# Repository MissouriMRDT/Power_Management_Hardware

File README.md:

# Power_Management_Hardware
Monitors health of the battery and distributes power to the rover's electronics

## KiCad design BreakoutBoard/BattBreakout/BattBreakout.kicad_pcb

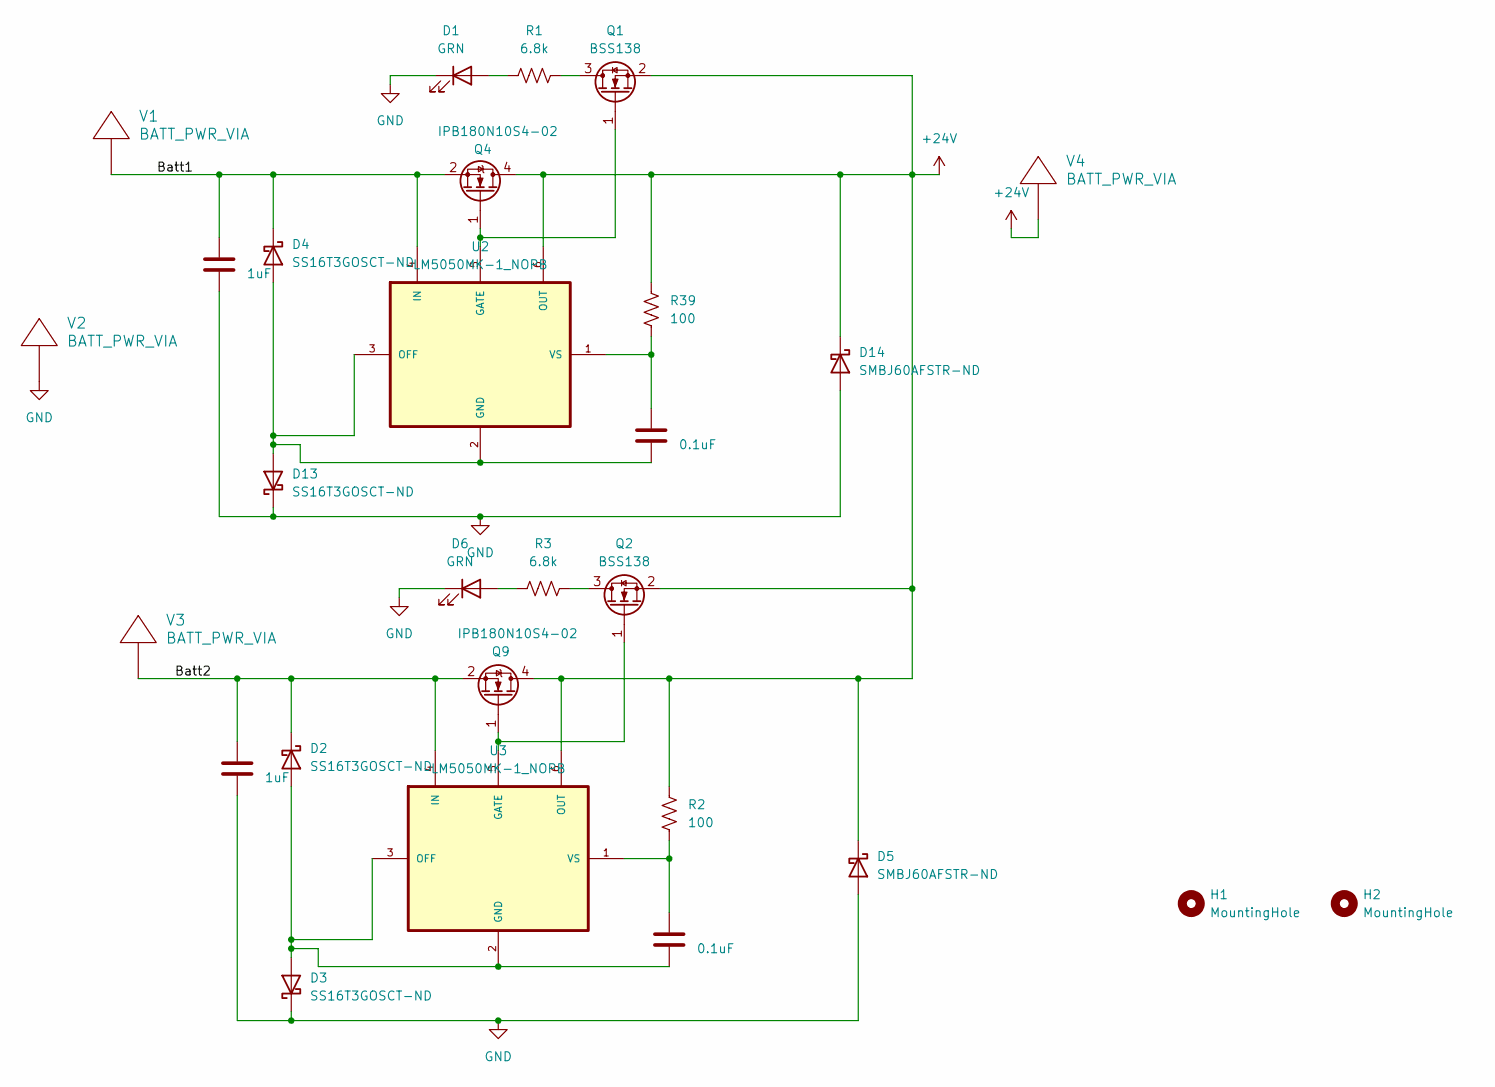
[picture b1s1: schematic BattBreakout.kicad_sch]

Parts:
C5, C11: 1uF; C_0603_1608Metric_Pad1.08x0.95mm_HandSolder
C10, C12: 0.1uF; C_0603_1608Metric_Pad1.08x0.95mm_HandSolder
D1, D6: GRN; LED_0201_0603Metric_Pad0.64x0.40mm_HandSolder
D2, D3, D4, D13: SS16T3GOSCT-ND; D_SMA
D5, D14: SMBJ60AFSTR-ND; D_SMB
H1, H2: MountingHole; 4_40_Hole_Corner
Q1, Q2: BSS138; SOT-23W_Handsoldering
Q4, Q9: IPB180N10S4-02; TO-263-6
R1, R3: 6.8k; R_0201_0603Metric_Pad0.64x0.40mm_HandSolder
R2, R39: 100; R_0201_0603Metric_Pad0.64x0.40mm_HandSolder
U2, U3: LM5050MK-1_NOPB; SOT95P280X110-6N
V1, V2, V3, V4: BATT_PWR_VIA

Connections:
+24V: D5.1 (K), D14.1 (K), Q1.2 (S), Q2.2 (S), Q4.4 (D), Q9.4 (D), R2.2, R39.2, U2.6 (OUT), U3.6 (OUT), V4.1
/Batt1: C11.1, D4.1 (K), Q4.2 (S), Q4.3 (S), Q4.5 (S), Q4.6 (S), Q4.7 (S), U2.4 (IN), V1.1
/Batt2: C5.1, D2.1 (K), Q9.2 (S), Q9.3 (S), Q9.5 (S), Q9.6 (S), Q9.7 (S), U3.4 (IN), V3.1
GND: C5.2, C11.2, D1.1 (K), D3.1 (K), D5.2 (A), D6.1 (K), D13.1 (K), D14.2 (A), V2.1
unnamed: D1.2 (A), R1.1
unnamed: C10.2, D2.2 (A), D3.2 (A), U3.2 (GND), U3.3 (OFF)
unnamed: D6.2 (A), R3.1
unnamed: C12.2, D4.2 (A), D13.2 (A), U2.2 (GND), U2.3 (OFF)
unnamed: Q1.3 (D), R1.2
unnamed: Q1.1 (G), Q4.1 (G), U2.5 (GATE)
unnamed: Q2.3 (D), R3.2
unnamed: Q2.1 (G), Q9.1 (G), U3.5 (GATE)
unnamed: C12.1, R39.1, U2.1 (VS)
unnamed: C10.1, R2.1, U3.1 (VS)

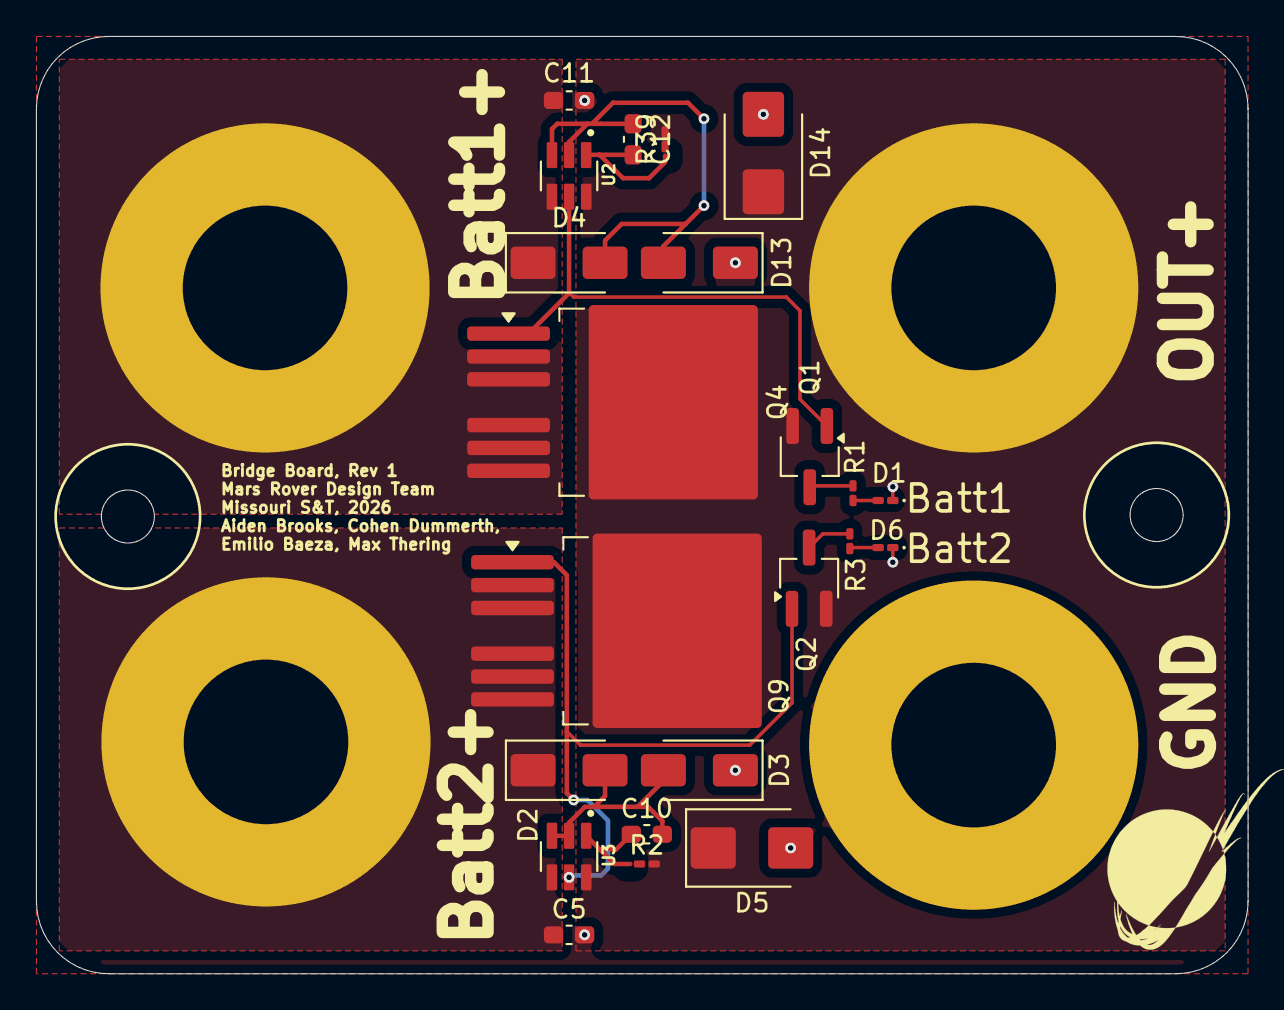
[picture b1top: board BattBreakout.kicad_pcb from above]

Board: 2 copper layers, 67.3 x 52.1 mm, 29 parts (0 on the bottom side), 14 nets.

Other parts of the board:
G1: LOGO; 0_MRDT_Logo_10mm

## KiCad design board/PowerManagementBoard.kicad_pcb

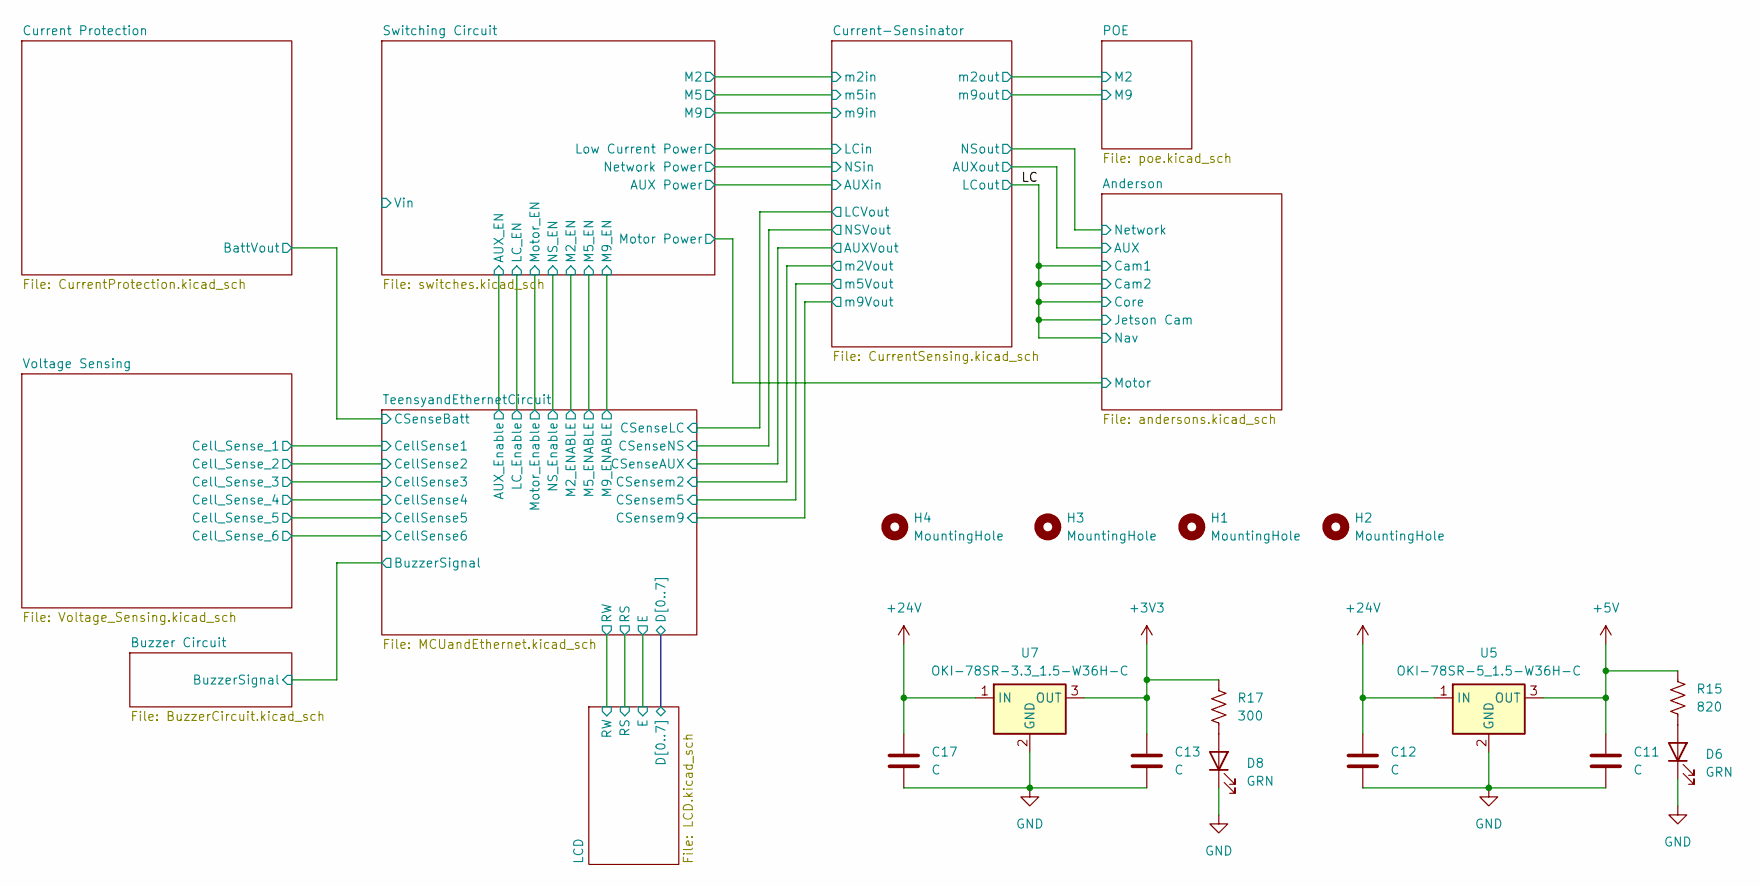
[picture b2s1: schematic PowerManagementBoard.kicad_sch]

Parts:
C11, C12, C13, C17: C; C_0603_1608Metric_Pad1.08x0.95mm_HandSolder
D6, D8: GRN; LED_0603_1608Metric_Pad1.05x0.95mm_HandSolder
H1, H2, H3, H4: MountingHole; 4_40_Hole
R15: 820; R_0603_1608Metric_Pad0.98x0.95mm_HandSolder
R17: 300; R_0603_1608Metric_Pad0.98x0.95mm_HandSolder
U5: OKI-78SR-5_1.5-W36H-C; Converter_DCDC_Murata_OKI-78SR_Horizontal
U7: OKI-78SR-3.3_1.5-W36H-C; Converter_DCDC_Murata_OKI-78SR_Horizontal

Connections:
+3V3: C13.1, R17.1, U7.3 (OUT); also elsewhere on the board
+5V: C11.1, R15.1, U5.3 (OUT); also elsewhere on the board
+24V: C12.1, C17.1, U5.1 (IN), U7.1 (IN); also elsewhere on the board
GND: C11.2, C12.2, C13.2, C17.2, D6.1 (K), D8.1 (K), U5.2 (GND), U7.2 (GND); also elsewhere on the board
unnamed: D6.2 (A), R15.2
unnamed: D8.2 (A), R17.2

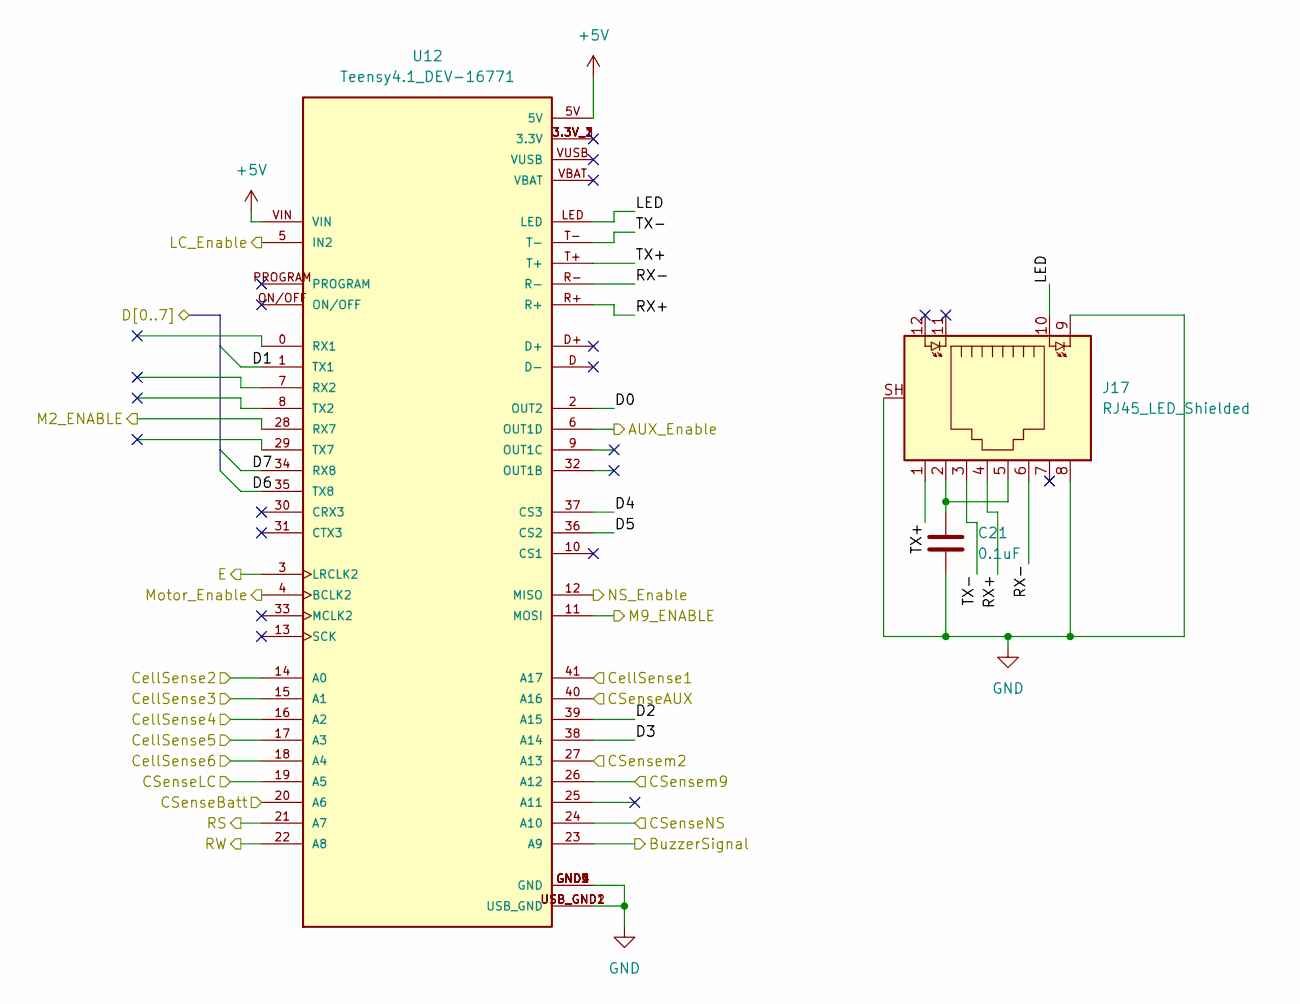
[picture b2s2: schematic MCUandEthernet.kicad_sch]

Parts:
C21: 0.1uF; C_0603_1608Metric_Pad1.08x0.95mm_HandSolder
J17: RJ45_LED_Shielded; RJ45_Teensy
U12: Teensy4.1_DEV-16771; Teensy_4_1_Ethernet; PARTREV 4.1

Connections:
+5V: U12.5V, U12.VIN; also elsewhere on the board
/Buzzer Circuit/BuzzerSignal: U12.23 (A9); also elsewhere on the board
/Current Protection/BattVout: U12.20 (A6); also elsewhere on the board
/Current-Sensinator/AUXVout: U12.40 (A16); also elsewhere on the board
/Current-Sensinator/LCVout: U12.19 (A5); also elsewhere on the board
/Current-Sensinator/NSVout: U12.24 (A10); also elsewhere on the board
/Current-Sensinator/m2Vout: U12.27 (A13); also elsewhere on the board
/Current-Sensinator/m9Vout: U12.26 (A12); also elsewhere on the board
/LCD/D0: U12.2 (OUT2); also elsewhere on the board
/LCD/D1: U12.1 (TX1); also elsewhere on the board
/LCD/D2: U12.39 (A15); also elsewhere on the board
/LCD/D3: U12.38 (A14); also elsewhere on the board
/LCD/D4: U12.37 (CS3); also elsewhere on the board
/LCD/D5: U12.36 (CS2); also elsewhere on the board
/LCD/D6: U12.35 (TX8); also elsewhere on the board
/LCD/D7: U12.34 (RX8); also elsewhere on the board
/LCD/E: U12.3 (LRCLK2); also elsewhere on the board
/LCD/RS: U12.21 (A7); also elsewhere on the board
/LCD/RW: U12.22 (A8); also elsewhere on the board
/Switching Circuit/AUX_EN: U12.6 (OUT1D); also elsewhere on the board
/Switching Circuit/LC_EN: U12.5 (IN2); also elsewhere on the board
/Switching Circuit/M2_EN: U12.28 (RX7); also elsewhere on the board
/Switching Circuit/M9_EN: U12.11 (MOSI); also elsewhere on the board
/Switching Circuit/Motor_EN: U12.4 (BCLK2); also elsewhere on the board
/Switching Circuit/NS_EN: U12.12 (MISO); also elsewhere on the board
/TeensyandEthernetCircuit/CellSense1: U12.41 (A17); also elsewhere on the board
/TeensyandEthernetCircuit/CellSense2: U12.14 (A0); also elsewhere on the board
/TeensyandEthernetCircuit/CellSense3: U12.15 (A1); also elsewhere on the board
/TeensyandEthernetCircuit/CellSense4: U12.16 (A2); also elsewhere on the board
/TeensyandEthernetCircuit/CellSense5: U12.17 (A3); also elsewhere on the board
/TeensyandEthernetCircuit/CellSense6: U12.18 (A4); also elsewhere on the board
/TeensyandEthernetCircuit/LED: J17.10, U12.LED
/TeensyandEthernetCircuit/RX+: J17.4, U12.R+
/TeensyandEthernetCircuit/RX-: J17.6, U12.R-
/TeensyandEthernetCircuit/TX+: J17.1, U12.T+
/TeensyandEthernetCircuit/TX-: J17.3, U12.T-
GND: C21.2, J17.8, J17.9, J17.SH, U12.GND1 (GND), U12.GND2 (GND), U12.GND3 (GND), U12.GND4 (GND), U12.GND5 (GND), U12.USB_GND1 (USB_GND), U12.USB_GND2 (USB_GND); also elsewhere on the board
unnamed: C21.1, J17.2, J17.5

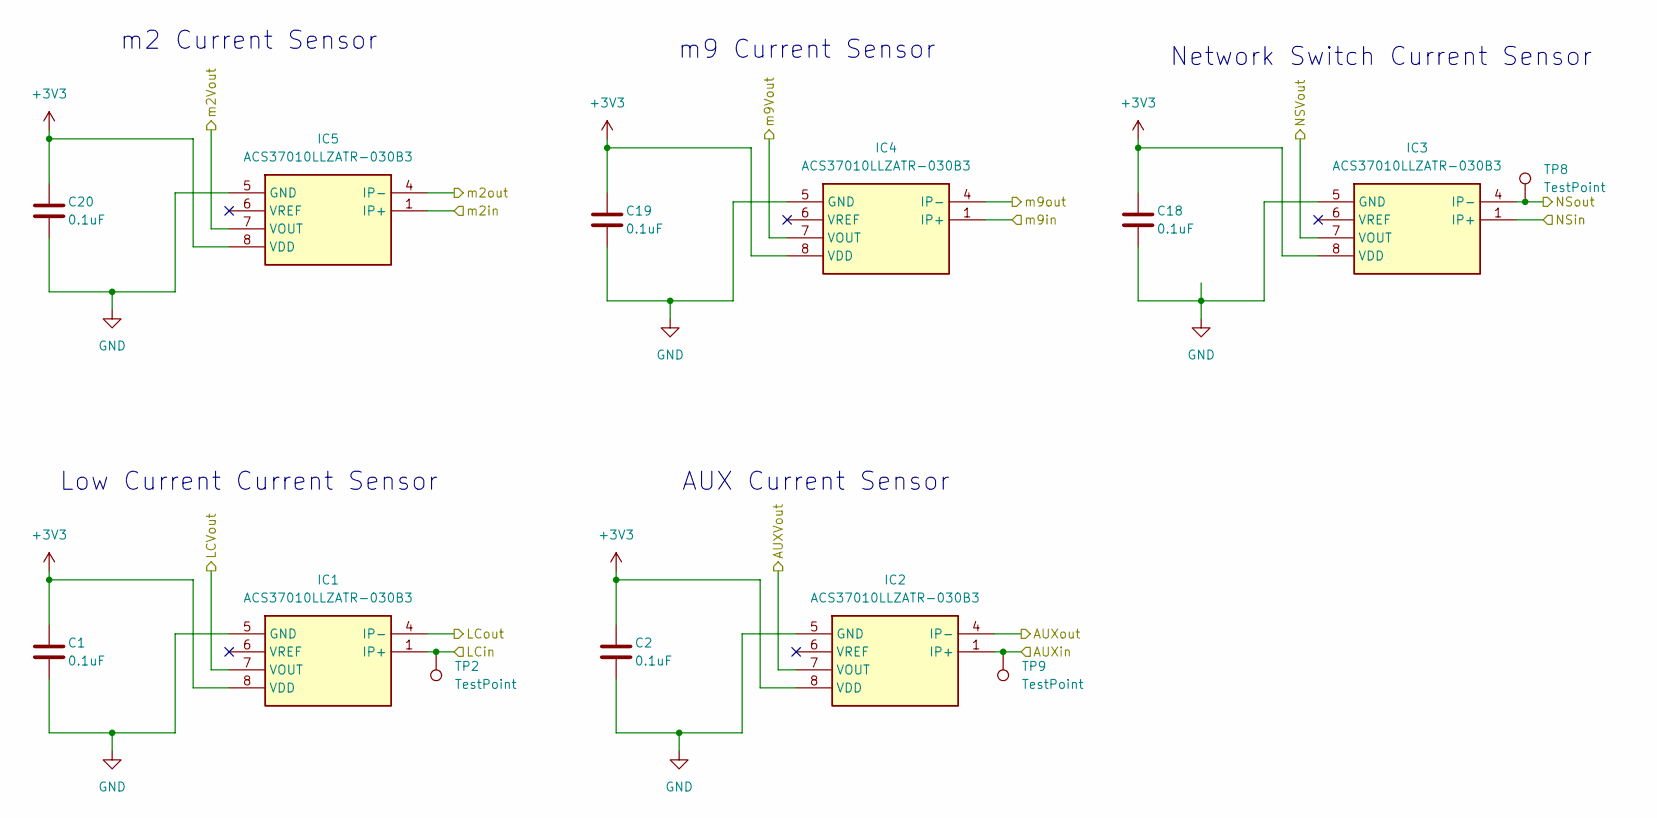
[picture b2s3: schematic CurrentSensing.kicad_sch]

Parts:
C1, C2, C18, C19, C20: 0.1uF; C_0603_1608Metric_Pad1.08x0.95mm_HandSolder
IC1, IC2, IC3, IC4, IC5: ACS37010LLZATR-030B3; IC_ACS37030LLZATR-040B3; Mouser Part Number 250-37010LLZATR030B3
TP2, TP8, TP9: TestPoint; TestPoint_Pad_D1.0mm

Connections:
+3V3: C1.1, C2.1, C18.1, C19.1, C20.1, IC1.8 (VDD), IC2.8 (VDD), IC3.8 (VDD), IC4.8 (VDD), IC5.8 (VDD); also elsewhere on the board
/Anderson/AUX: IC2.4 (IP-); also elsewhere on the board
/Anderson/Network: IC3.4 (IP-), TP8.1; also elsewhere on the board
/Current-Sensinator/AUXVout: IC2.7 (VOUT); also elsewhere on the board
/Current-Sensinator/AUXin: IC2.1 (IP+), TP9.1; also elsewhere on the board
/Current-Sensinator/LCVout: IC1.7 (VOUT); also elsewhere on the board
/Current-Sensinator/LCin: IC1.1 (IP+), TP2.1; also elsewhere on the board
/Current-Sensinator/NSVout: IC3.7 (VOUT); also elsewhere on the board
/Current-Sensinator/NSin: IC3.1 (IP+); also elsewhere on the board
/Current-Sensinator/m2Vout: IC5.7 (VOUT); also elsewhere on the board
/Current-Sensinator/m2in: IC5.1 (IP+); also elsewhere on the board
/Current-Sensinator/m2out: IC5.4 (IP-); also elsewhere on the board
/Current-Sensinator/m9Vout: IC4.7 (VOUT); also elsewhere on the board
/Current-Sensinator/m9in: IC4.1 (IP+); also elsewhere on the board
/Current-Sensinator/m9out: IC4.4 (IP-); also elsewhere on the board
/LC: IC1.4 (IP-); also elsewhere on the board
GND: C1.2, C2.2, C18.2, C19.2, C20.2, IC1.5 (GND), IC2.5 (GND), IC3.5 (GND), IC4.5 (GND), IC5.5 (GND); also elsewhere on the board

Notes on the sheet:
Low Current Current Sensor
AUX Current Sensor
m2 Current Sensor
Network Switch Current Sensor
m9 Current Sensor

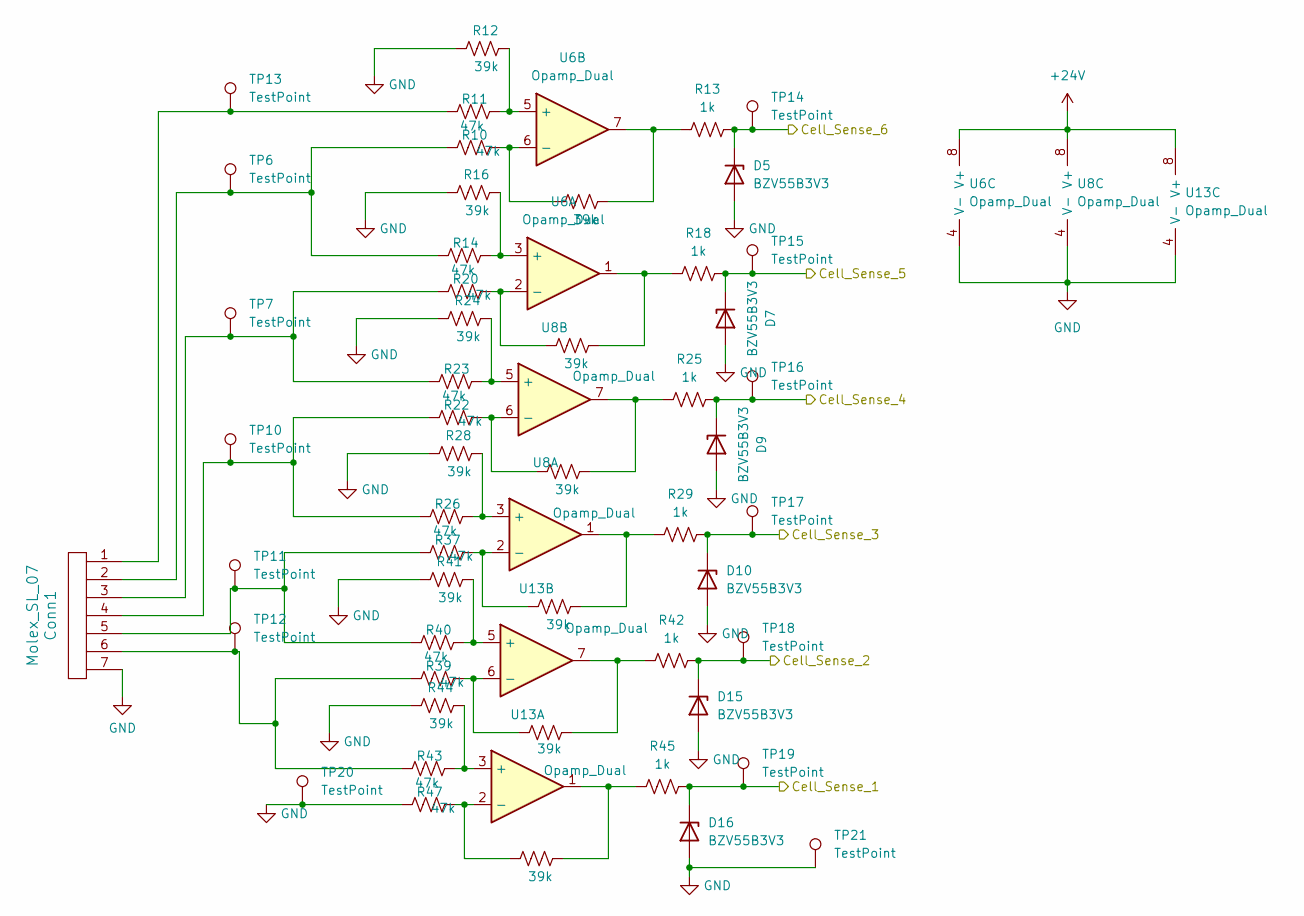
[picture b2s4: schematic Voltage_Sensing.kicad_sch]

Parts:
Conn1: Molex_SL_07; MOLEX_SL_07_Vertical
D5, D7, D9, D10, D15, D16: BZV55B3V3; D_MiniMELF
R9, R12, R16, R19, R21, R24, R28, R36, R38, R41, R44, R46: 39k; R_0603_1608Metric_Pad0.98x0.95mm_HandSolder
R10, R11, R14, R20, R22, R23, R26, R37, R39, R40, R43, R47: 47k; R_0603_1608Metric_Pad0.98x0.95mm_HandSolder
R13, R18, R25, R29, R42, R45: 1k; R_0603_1608Metric_Pad0.98x0.95mm_HandSolder
TP6, TP7, TP10, TP11, TP12, TP13, TP14, TP15, TP16, TP17, TP18, TP19, TP20, TP21: TestPoint; TestPoint_Pad_D1.0mm
U6, U8, U13: Opamp_Dual; SOIC127P600X175-8N

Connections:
+24V: U6.8 (V+), U8.8 (V+), U13.8 (V+); also elsewhere on the board
/TeensyandEthernetCircuit/CellSense1: D16.1 (K), R45.2, TP19.1; also elsewhere on the board
/TeensyandEthernetCircuit/CellSense2: D15.1 (K), R42.2, TP18.1; also elsewhere on the board
/TeensyandEthernetCircuit/CellSense3: D10.1 (K), R29.2, TP17.1; also elsewhere on the board
/TeensyandEthernetCircuit/CellSense4: D9.1 (K), R25.2, TP16.1; also elsewhere on the board
/TeensyandEthernetCircuit/CellSense5: D7.1 (K), R18.2, TP15.1; also elsewhere on the board
/TeensyandEthernetCircuit/CellSense6: D5.1 (K), R13.2, TP14.1; also elsewhere on the board
GND: Conn1.7, D5.2 (A), D7.2 (A), D9.2 (A), D10.2 (A), D15.2 (A), D16.2 (A), R12.2, R16.2, R24.2, R28.2, R41.2, R44.2, R47.2, TP20.1, TP21.1, U6.4 (V-), U8.4 (V-), U13.4 (V-); also elsewhere on the board
unnamed: Conn1.1, R11.2, TP13.1
unnamed: Conn1.2, R10.2, R14.2, TP6.1
unnamed: Conn1.3, R20.2, R23.2, TP7.1
unnamed: Conn1.4, R22.2, R26.2, TP10.1
unnamed: Conn1.5, R37.2, R40.2, TP11.1
unnamed: Conn1.6, R39.2, R43.2, TP12.1
unnamed: R9.1, R13.1, U6.7
unnamed: R18.1, R19.1, U6.1
unnamed: R21.1, R25.1, U8.7
unnamed: R29.1, R36.1, U8.1
unnamed: R38.1, R42.1, U13.7
unnamed: R45.1, R46.1, U13.1
unnamed: R14.1, R16.1, U6.3 (+)
unnamed: R19.2, R20.1, U6.2 (-)
unnamed: R11.1, R12.1, U6.5 (+)
unnamed: R9.2, R10.1, U6.6 (-)
unnamed: R26.1, R28.1, U8.3 (+)
unnamed: R36.2, R37.1, U8.2 (-)
unnamed: R23.1, R24.1, U8.5 (+)
unnamed: R21.2, R22.1, U8.6 (-)
unnamed: R43.1, R44.1, U13.3 (+)
unnamed: R46.2, R47.1, U13.2 (-)
unnamed: R40.1, R41.1, U13.5 (+)
unnamed: R38.2, R39.1, U13.6 (-)

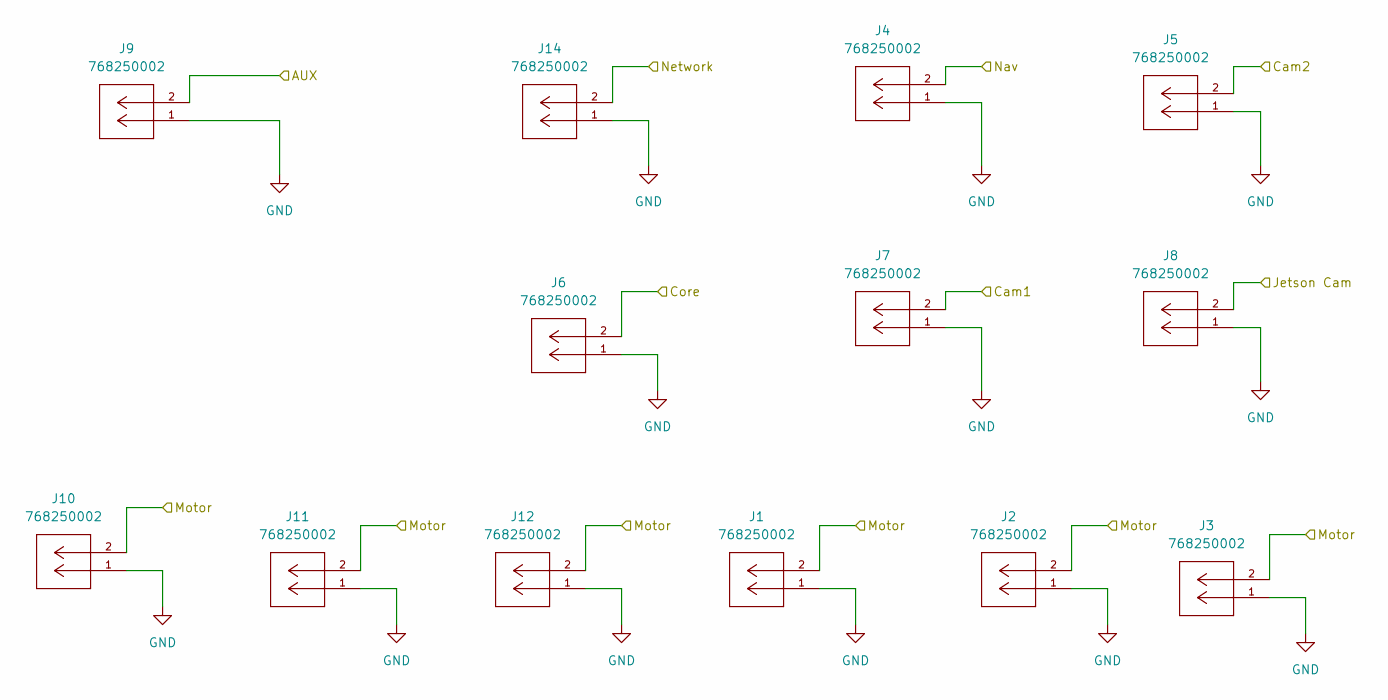
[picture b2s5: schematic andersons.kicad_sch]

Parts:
J1, J2, J3, J4, J5, J6, J7, J8, J9, J10, J11, J12, J14: 768250002; CONN_SD-76825-0100_02_MOL; MANUFACTURER_PART_NUMBER 768250002

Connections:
/Anderson/AUX: J9.2; also elsewhere on the board
/Anderson/Motor: J1.2, J2.2, J3.2, J10.2, J11.2, J12.2; also elsewhere on the board
/Anderson/Network: J14.2; also elsewhere on the board
/LC: J4.2, J5.2, J6.2, J7.2, J8.2; also elsewhere on the board
GND: J1.1, J2.1, J3.1, J4.1, J5.1, J6.1, J7.1, J8.1, J9.1, J10.1, J11.1, J12.1, J14.1; also elsewhere on the board

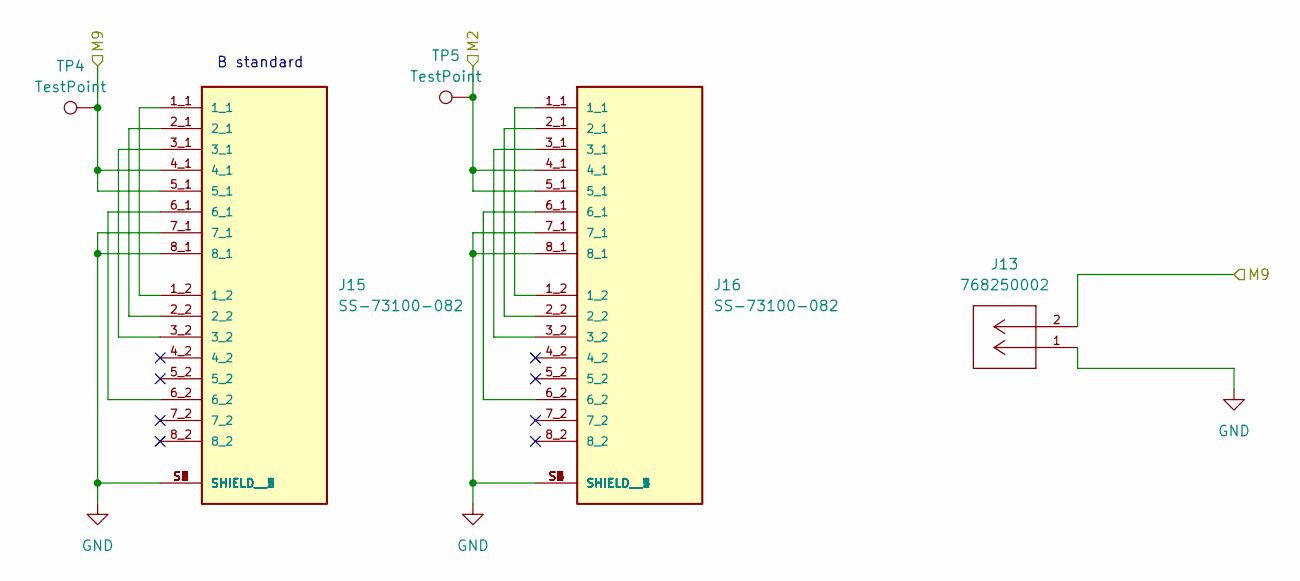
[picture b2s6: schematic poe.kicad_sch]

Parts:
J13: 768250002; CONN_SD-76825-0100_02_MOL; MANUFACTURER_PART_NUMBER 768250002
J15, J16: SS-73100-082; BEL_SS-73100-082; PARTREV A0
TP4, TP5: TestPoint; TestPoint_Pad_D1.0mm

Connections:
/Current-Sensinator/m2out: J16.4_1, J16.5_1, TP5.1; also elsewhere on the board
/Current-Sensinator/m9out: J13.2, J15.4_1, J15.5_1, TP4.1; also elsewhere on the board
GND: J13.1, J15.7_1, J15.8_1, J15.S1 (SHIELD), J15.S2 (SHIELD__1), J15.S3 (SHIELD__2), J15.S4 (SHIELD__3), J15.S5 (SHIELD__4), J15.S6 (SHIELD__5), J16.7_1, J16.8_1, J16.S1 (SHIELD), J16.S2 (SHIELD__1), J16.S3 (SHIELD__2), J16.S4 (SHIELD__3), J16.S5 (SHIELD__4), J16.S6 (SHIELD__5); also elsewhere on the board
unnamed: J15.1_1, J15.1_2
unnamed: J15.2_1, J15.2_2
unnamed: J15.3_1, J15.3_2
unnamed: J15.6_1, J15.6_2
unnamed: J16.1_1, J16.1_2
unnamed: J16.2_1, J16.2_2
unnamed: J16.3_1, J16.3_2
unnamed: J16.6_1, J16.6_2

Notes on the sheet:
B standard

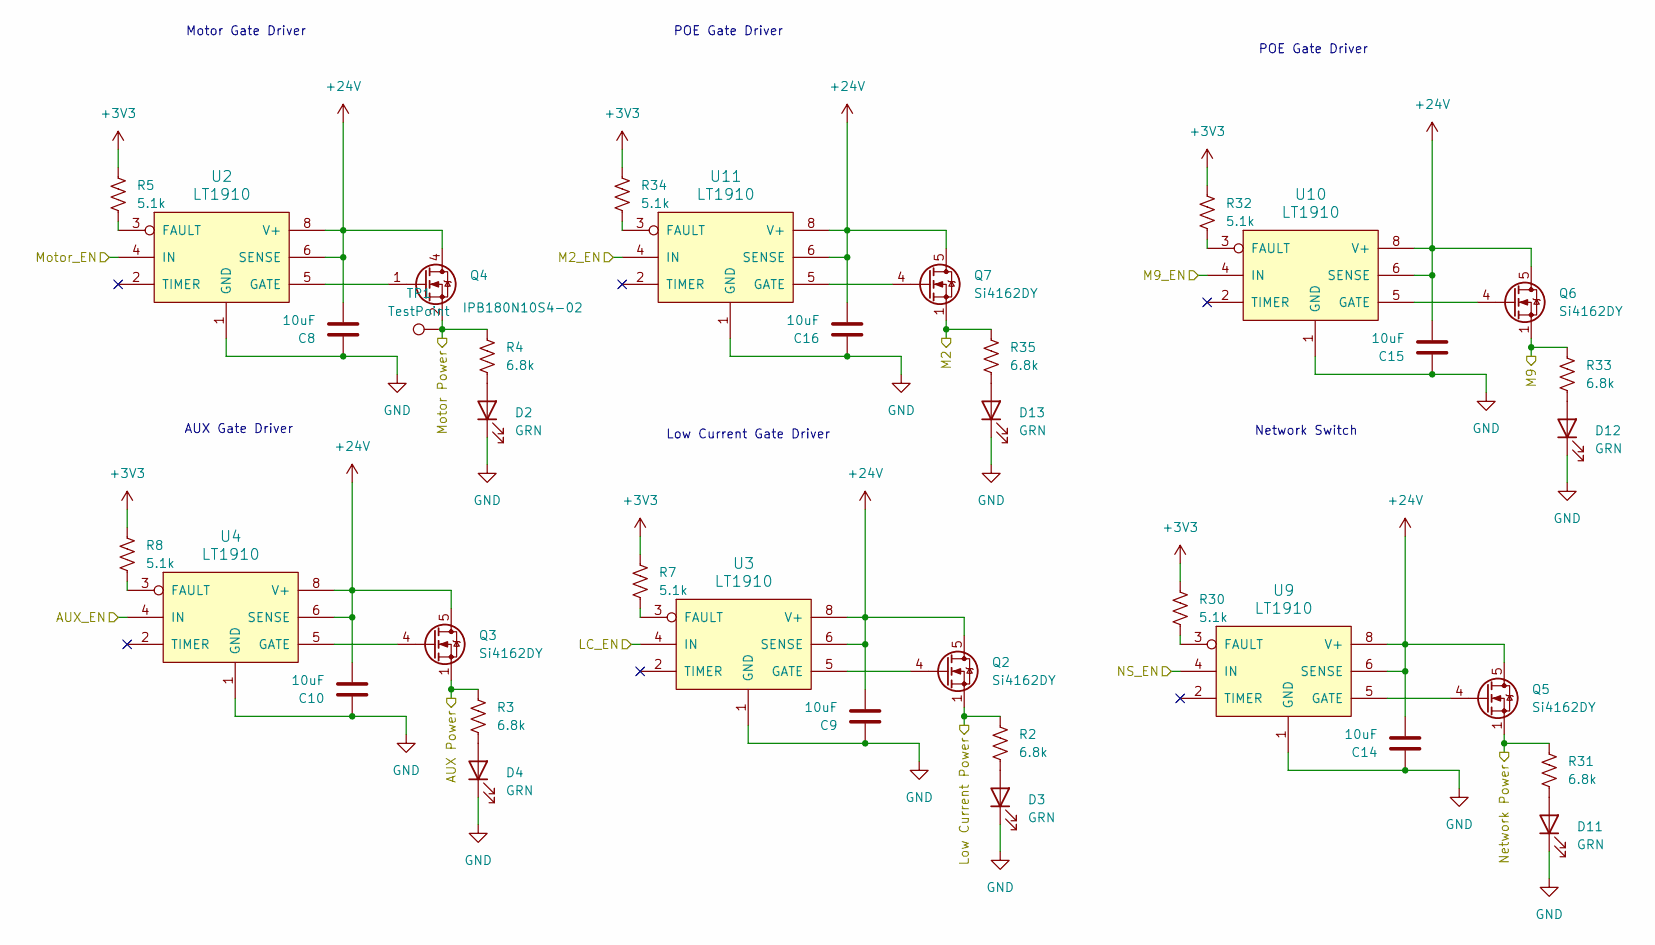
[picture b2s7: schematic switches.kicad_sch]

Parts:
C8, C9, C10, C14, C15, C16: 10uF; C_0603_1608Metric_Pad1.08x0.95mm_HandSolder
D2, D3, D4, D11, D12, D13: GRN; LED_0603_1608Metric_Pad1.05x0.95mm_HandSolder
Q2, Q3, Q5, Q6, Q7: Si4162DY; SOIC-8_3.9x4.9mm_P1.27mm
Q4: IPB180N10S4-02; TO-263-6
R2, R3, R4, R31, R33, R35: 6.8k; R_0603_1608Metric_Pad0.98x0.95mm_HandSolder
R5, R7, R8, R30, R32, R34: 5.1k; R_0603_1608Metric_Pad0.98x0.95mm_HandSolder
TP1: TestPoint; TestPoint_Pad_D1.0mm
U2, U3, U4, U9, U10, U11: LT1910; SOIC-8_3.9x4.9mm_P1.27mm

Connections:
+3V3: R5.1, R7.1, R8.1, R30.1, R32.1, R34.1; also elsewhere on the board
+24V: C8.2, C9.2, C10.2, C14.2, C15.2, C16.2, Q2.5 (D), Q2.6 (D), Q2.7 (D), Q2.8 (D), Q3.5 (D), Q3.6 (D), Q3.7 (D), Q3.8 (D), Q4.4 (D), Q5.5 (D), Q5.6 (D), Q5.7 (D), Q5.8 (D), Q6.5 (D), Q6.6 (D), Q6.7 (D), Q6.8 (D), Q7.5 (D), Q7.6 (D), Q7.7 (D), Q7.8 (D), U2.6 (SENSE), U2.8 (V+), U3.6 (SENSE), U3.8 (V+), U4.6 (SENSE), U4.8 (V+), U9.6 (SENSE), U9.8 (V+), U10.6 (SENSE), U10.8 (V+), U11.6 (SENSE), U11.8 (V+); also elsewhere on the board
/Anderson/Motor: Q4.2 (S), Q4.3 (S), Q4.5 (S), Q4.6 (S), Q4.7 (S), R4.1, TP1.1; also elsewhere on the board
/Current-Sensinator/AUXin: Q3.1 (S), Q3.2 (S), Q3.3 (S), R3.1; also elsewhere on the board
/Current-Sensinator/LCin: Q2.1 (S), Q2.2 (S), Q2.3 (S), R2.1; also elsewhere on the board
/Current-Sensinator/NSin: Q5.1 (S), Q5.2 (S), Q5.3 (S), R31.1; also elsewhere on the board
/Current-Sensinator/m2in: Q7.1 (S), Q7.2 (S), Q7.3 (S), R35.1; also elsewhere on the board
/Current-Sensinator/m9in: Q6.1 (S), Q6.2 (S), Q6.3 (S), R33.1; also elsewhere on the board
/Switching Circuit/AUX_EN: U4.4 (IN); also elsewhere on the board
/Switching Circuit/LC_EN: U3.4 (IN); also elsewhere on the board
/Switching Circuit/M2_EN: U11.4 (IN); also elsewhere on the board
/Switching Circuit/M9_EN: U10.4 (IN); also elsewhere on the board
/Switching Circuit/Motor_EN: U2.4 (IN); also elsewhere on the board
/Switching Circuit/NS_EN: U9.4 (IN); also elsewhere on the board
GND: C8.1, C9.1, C10.1, C14.1, C15.1, C16.1, D2.1 (K), D3.1 (K), D4.1 (K), D11.1 (K), D12.1 (K), D13.1 (K), U2.1 (GND), U3.1 (GND), U4.1 (GND), U9.1 (GND), U10.1 (GND), U11.1 (GND); also elsewhere on the board
unnamed: D2.2 (A), R4.2
unnamed: D3.2 (A), R2.2
unnamed: D4.2 (A), R3.2
unnamed: D11.2 (A), R31.2
unnamed: D12.2 (A), R33.2
unnamed: D13.2 (A), R35.2
unnamed: Q2.4 (G), U3.5 (GATE)
unnamed: Q3.4 (G), U4.5 (GATE)
unnamed: Q4.1 (G), U2.5 (GATE)
unnamed: Q5.4 (G), U9.5 (GATE)
unnamed: Q6.4 (G), U10.5 (GATE)
unnamed: Q7.4 (G), U11.5 (GATE)
unnamed: R5.2, U2.3 (FAULT)
unnamed: R7.2, U3.3 (FAULT)
unnamed: R8.2, U4.3 (FAULT)
unnamed: R30.2, U9.3 (FAULT)
unnamed: R32.2, U10.3 (FAULT)
unnamed: R34.2, U11.3 (FAULT)

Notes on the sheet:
POE Gate Driver
Network Switch
AUX Gate Driver
Motor Gate Driver
Low Current Gate Driver

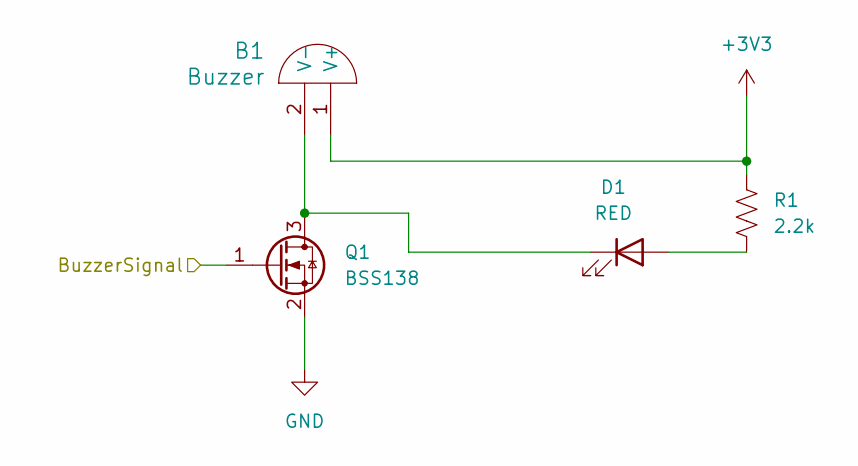
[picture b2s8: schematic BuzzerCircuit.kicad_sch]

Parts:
B1: Buzzer; Buzzer_12x9.5RM7.6
D1: RED; LED_0603_1608Metric_Pad1.05x0.95mm_HandSolder
Q1: BSS138; SOT-23
R1: 2.2k; R_0603_1608Metric_Pad0.98x0.95mm_HandSolder

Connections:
+3V3: B1.1 (V+), R1.1; also elsewhere on the board
/Buzzer Circuit/BuzzerSignal: Q1.1 (G); also elsewhere on the board
GND: Q1.2 (S); also elsewhere on the board
unnamed: B1.2 (V-), D1.1 (K), Q1.3 (D)
unnamed: D1.2 (A), R1.2

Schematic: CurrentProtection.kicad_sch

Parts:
C3, C4, C5: 1000uF; CP_Radial_D16.0mm_P7.50mm
C6: 1uF; C_0603_1608Metric_Pad1.08x0.95mm_HandSolder
C7: 0.1uF; C_0603_1608Metric_Pad1.08x0.95mm_HandSolder
D14: GRN; LED_0603_1608Metric_Pad1.05x0.95mm_HandSolder
R6: 4.7k; R_0603_1608Metric_Pad0.98x0.95mm_HandSolder
R27: 6.8k; R_0603_1608Metric_Pad0.98x0.95mm_HandSolder
TP3: TestPoint; TestPoint_Pad_D1.0mm
U1: ACS72981LLRATR-100U3; Allegro_PSOF-7_4.8x6.4mm_P1.60mm
V1, V2: BATT_PWR_VIA

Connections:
+3V3: C7.1, U1.1 (VCC); also elsewhere on the board
+24V: R27.1, TP3.1, U1.6 (IP-); also elsewhere on the board
/Current Protection/Batt1: C3.1, C4.1, C5.1, U1.5 (IP+), V2.1
/Current Protection/BattVout: C6.2, R6.2; also elsewhere on the board
GND: C3.2, C4.2, C5.2, C6.1, C7.2, D14.1 (K), U1.2 (GND), V1.1; also elsewhere on the board
unnamed: D14.2 (A), R27.2
unnamed: R6.1, U1.3 (VOUT)

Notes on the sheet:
LED CIRCUITS

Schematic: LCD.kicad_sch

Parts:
LCD1: NHD-0420H1Z-FL-GBW-33V3; LCD_NHD-0420H1Z-FL-GBW-33V3; PARTREV 02

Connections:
+3V3: LCD1.2 (VDD), LCD1.15 (A); also elsewhere on the board
/LCD/D0: LCD1.7 (DB0); also elsewhere on the board
/LCD/D1: LCD1.8 (DB1); also elsewhere on the board
/LCD/D2: LCD1.9 (DB2); also elsewhere on the board
/LCD/D3: LCD1.10 (DB3); also elsewhere on the board
/LCD/D4: LCD1.11 (DB4); also elsewhere on the board
/LCD/D5: LCD1.12 (DB5); also elsewhere on the board
/LCD/D6: LCD1.13 (DB6); also elsewhere on the board
/LCD/D7: LCD1.14 (DB7); also elsewhere on the board
/LCD/E: LCD1.6 (~E); also elsewhere on the board
/LCD/RS: LCD1.4 (RS); also elsewhere on the board
/LCD/RW: LCD1.5 (RW); also elsewhere on the board
GND: LCD1.1 (VSS), LCD1.3 (V0), LCD1.16 (K); also elsewhere on the board

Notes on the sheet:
Dpin

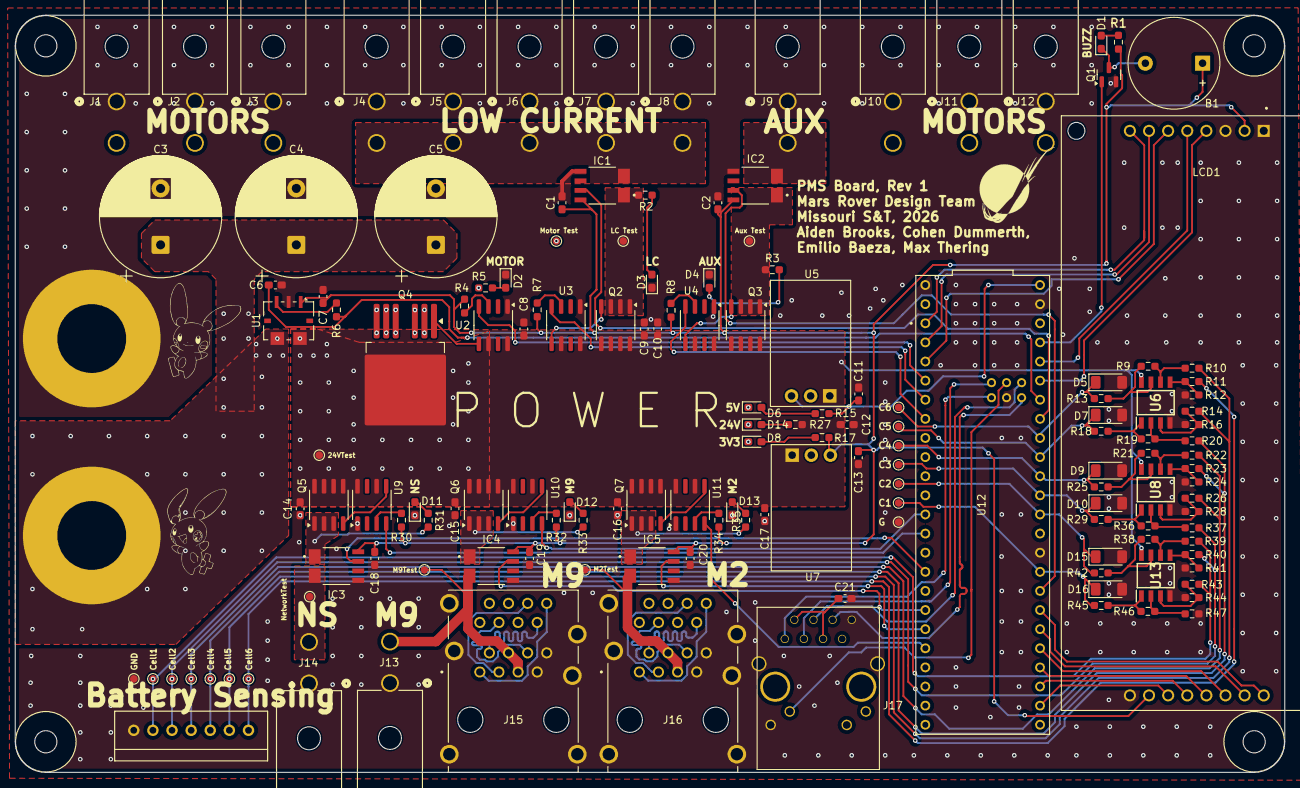
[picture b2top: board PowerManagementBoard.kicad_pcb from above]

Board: 2 copper layers, 168.7 x 100.6 mm, 160 parts (1 on the bottom side), 108 nets.

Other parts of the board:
G1: LOGO; 0_MRDT_Logo_10mm
G2, G5, G7: LOGO
